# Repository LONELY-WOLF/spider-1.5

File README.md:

# spider-1.5
Everything about hexapod robot

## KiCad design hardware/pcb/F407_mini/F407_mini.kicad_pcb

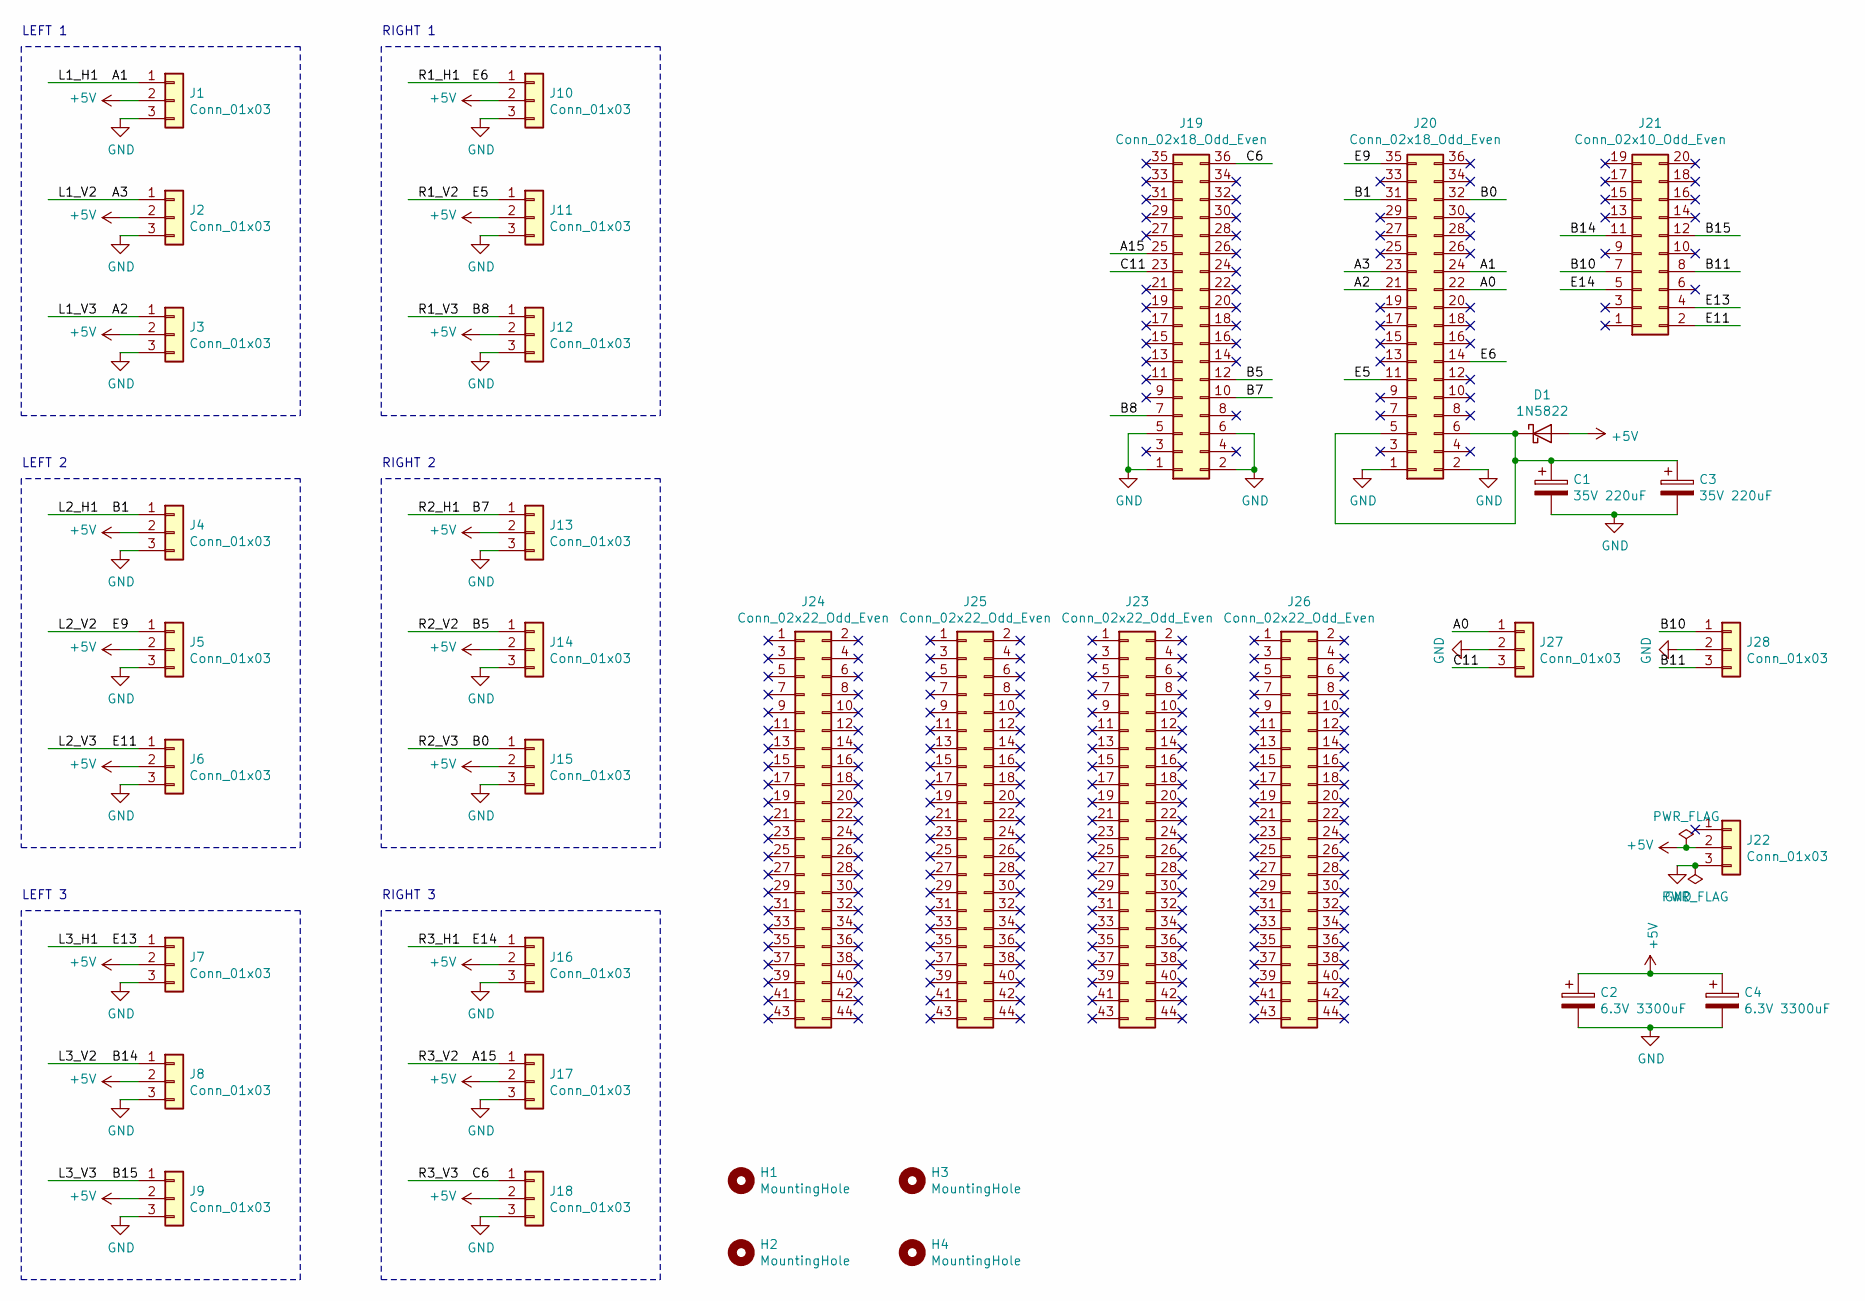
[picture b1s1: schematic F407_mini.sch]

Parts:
C1, C3: 35V 220uF; CP_Radial_D8.0mm_P3.80mm
C2, C4: 6.3V 3300uF; CP_Radial_D10.0mm_P5.00mm
D1: 1N5822; D_DO-201AD_P15.24mm_Horizontal
H1, H2, H3, H4: MountingHole; MountingHole_3.2mm_M3_Pad_Via
J1, J2, J3, J4, J5, J6, J7, J8, J9, J10, J11, J12, J13, J14, J15, J16, J17, J18, J22, J27, J28: Conn_01x03; PinHeader_1x03_P2.54mm_Vertical
J19, J20: Conn_02x18_Odd_Even; PinSocket_2x18_P2.54mm_Vertical
J21: Conn_02x10_Odd_Even; PinSocket_2x10_P2.54mm_Vertical
J23, J24, J25, J26: Conn_02x22_Odd_Even; PinHeader_2x22_P2.54mm_Vertical

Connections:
+5V: C2.1, C4.1, D1.2 (A), J1.2, J2.2, J3.2, J4.2, J5.2, J6.2, J7.2, J8.2, J9.2, J10.2, J11.2, J12.2, J13.2, J14.2, J15.2, J16.2, J17.2, J18.2, J22.2
/A0: J20.22, J27.1
/A1: J1.1, J20.24
/A2: J3.1, J20.21
/A3: J2.1, J20.23
/A15: J17.1, J19.25
/B0: J15.1, J20.32
/B1: J4.1, J20.31
/B5: J14.1, J19.12
/B7: J13.1, J19.10
/B8: J12.1, J19.7
/B10: J21.7, J28.1
/B11: J21.8, J28.3
/B14: J8.1, J21.11
/B15: J9.1, J21.12
/C6: J18.1, J19.36
/C11: J19.23, J27.3
/E5: J11.1, J20.11
/E6: J10.1, J20.14
/E9: J5.1, J20.35
/E11: J6.1, J21.2
/E13: J7.1, J21.4
/E14: J16.1, J21.5
GND: C1.2, C2.2, C3.2, C4.2, J1.3, J2.3, J3.3, J4.3, J5.3, J6.3, J7.3, J8.3, J9.3, J10.3, J11.3, J12.3, J13.3, J14.3, J15.3, J16.3, J17.3, J18.3, J19.1, J19.2, J19.5, J19.6, J20.1, J20.2, J22.3, J27.2, J28.2
unnamed: C1.1, C3.1, D1.1 (K), J20.5, J20.6

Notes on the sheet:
LEFT 1
LEFT 2
LEFT 3
RIGHT 1
RIGHT 2
RIGHT 3

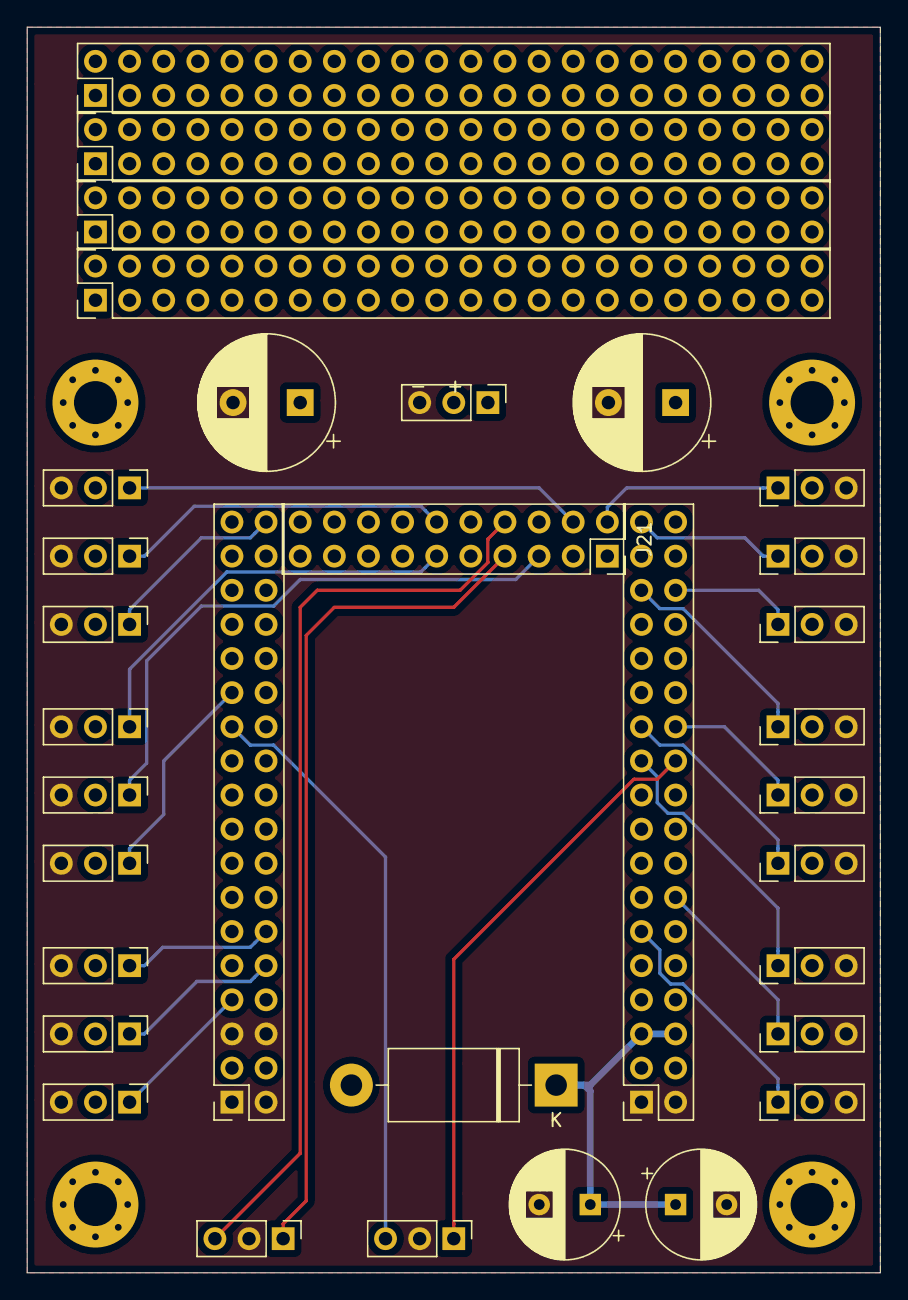
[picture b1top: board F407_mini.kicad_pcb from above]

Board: 2 copper layers, 63.5 x 92.7 mm, 37 parts (0 on the bottom side), 25 nets.

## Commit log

2020-01-19 Add PCB for F407 mini board
2020-01-20 flip connectors
2020-03-24 F407 mini board RC0
2020-03-27 add legacy firmware as module
